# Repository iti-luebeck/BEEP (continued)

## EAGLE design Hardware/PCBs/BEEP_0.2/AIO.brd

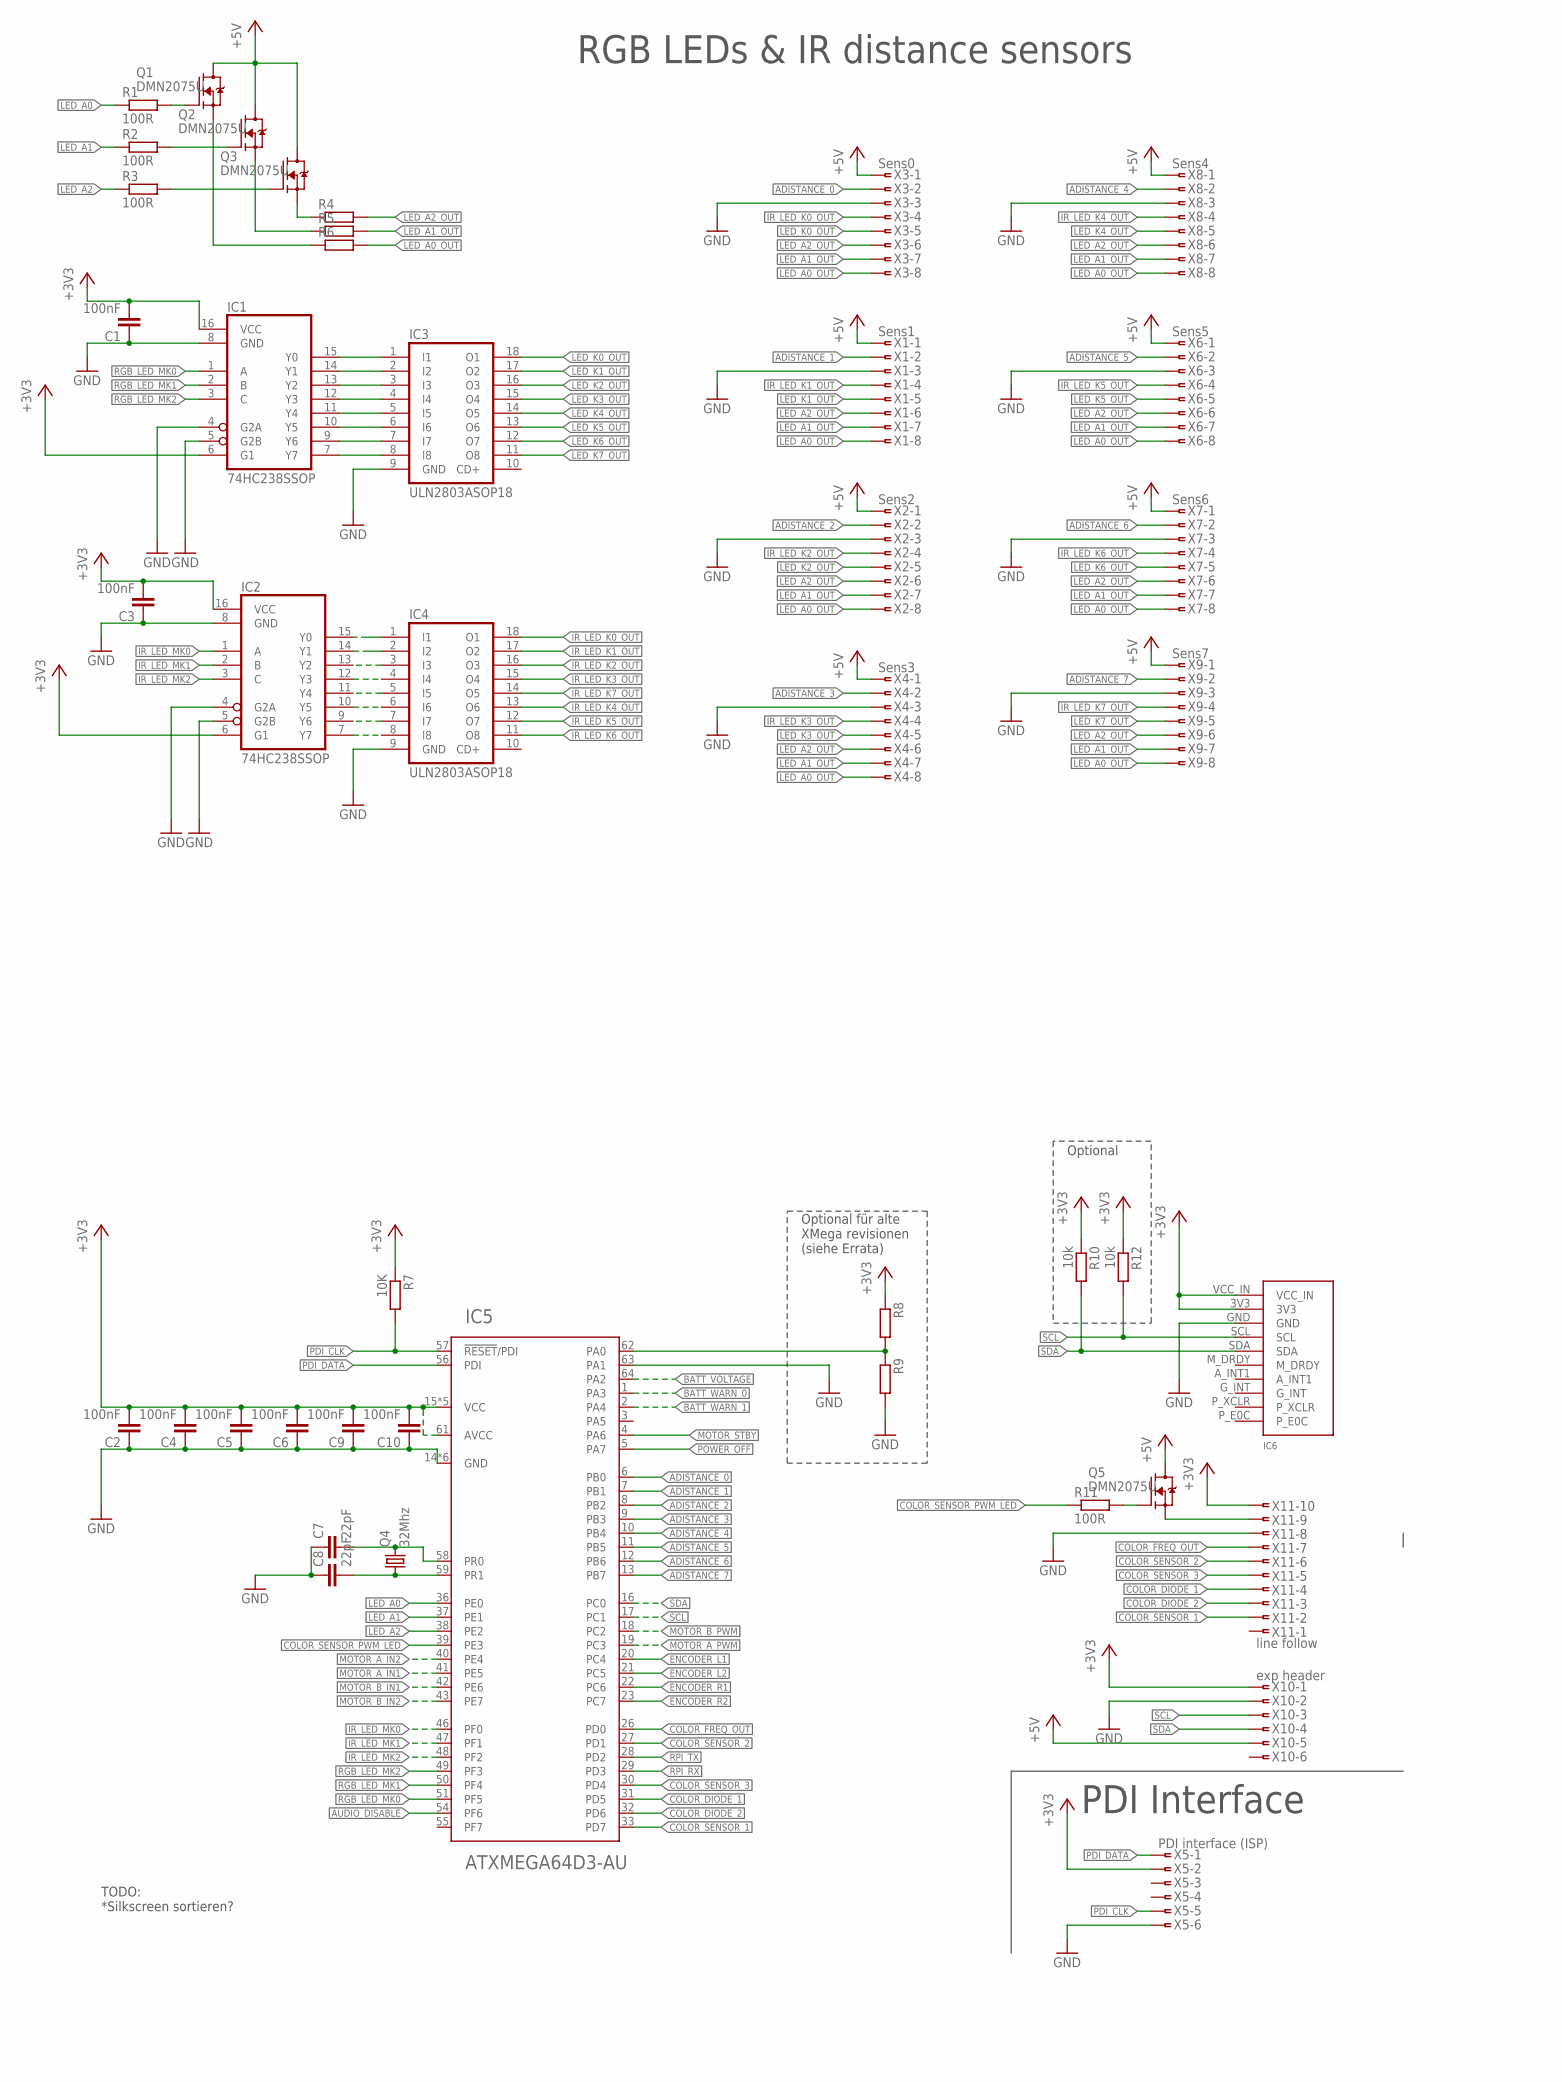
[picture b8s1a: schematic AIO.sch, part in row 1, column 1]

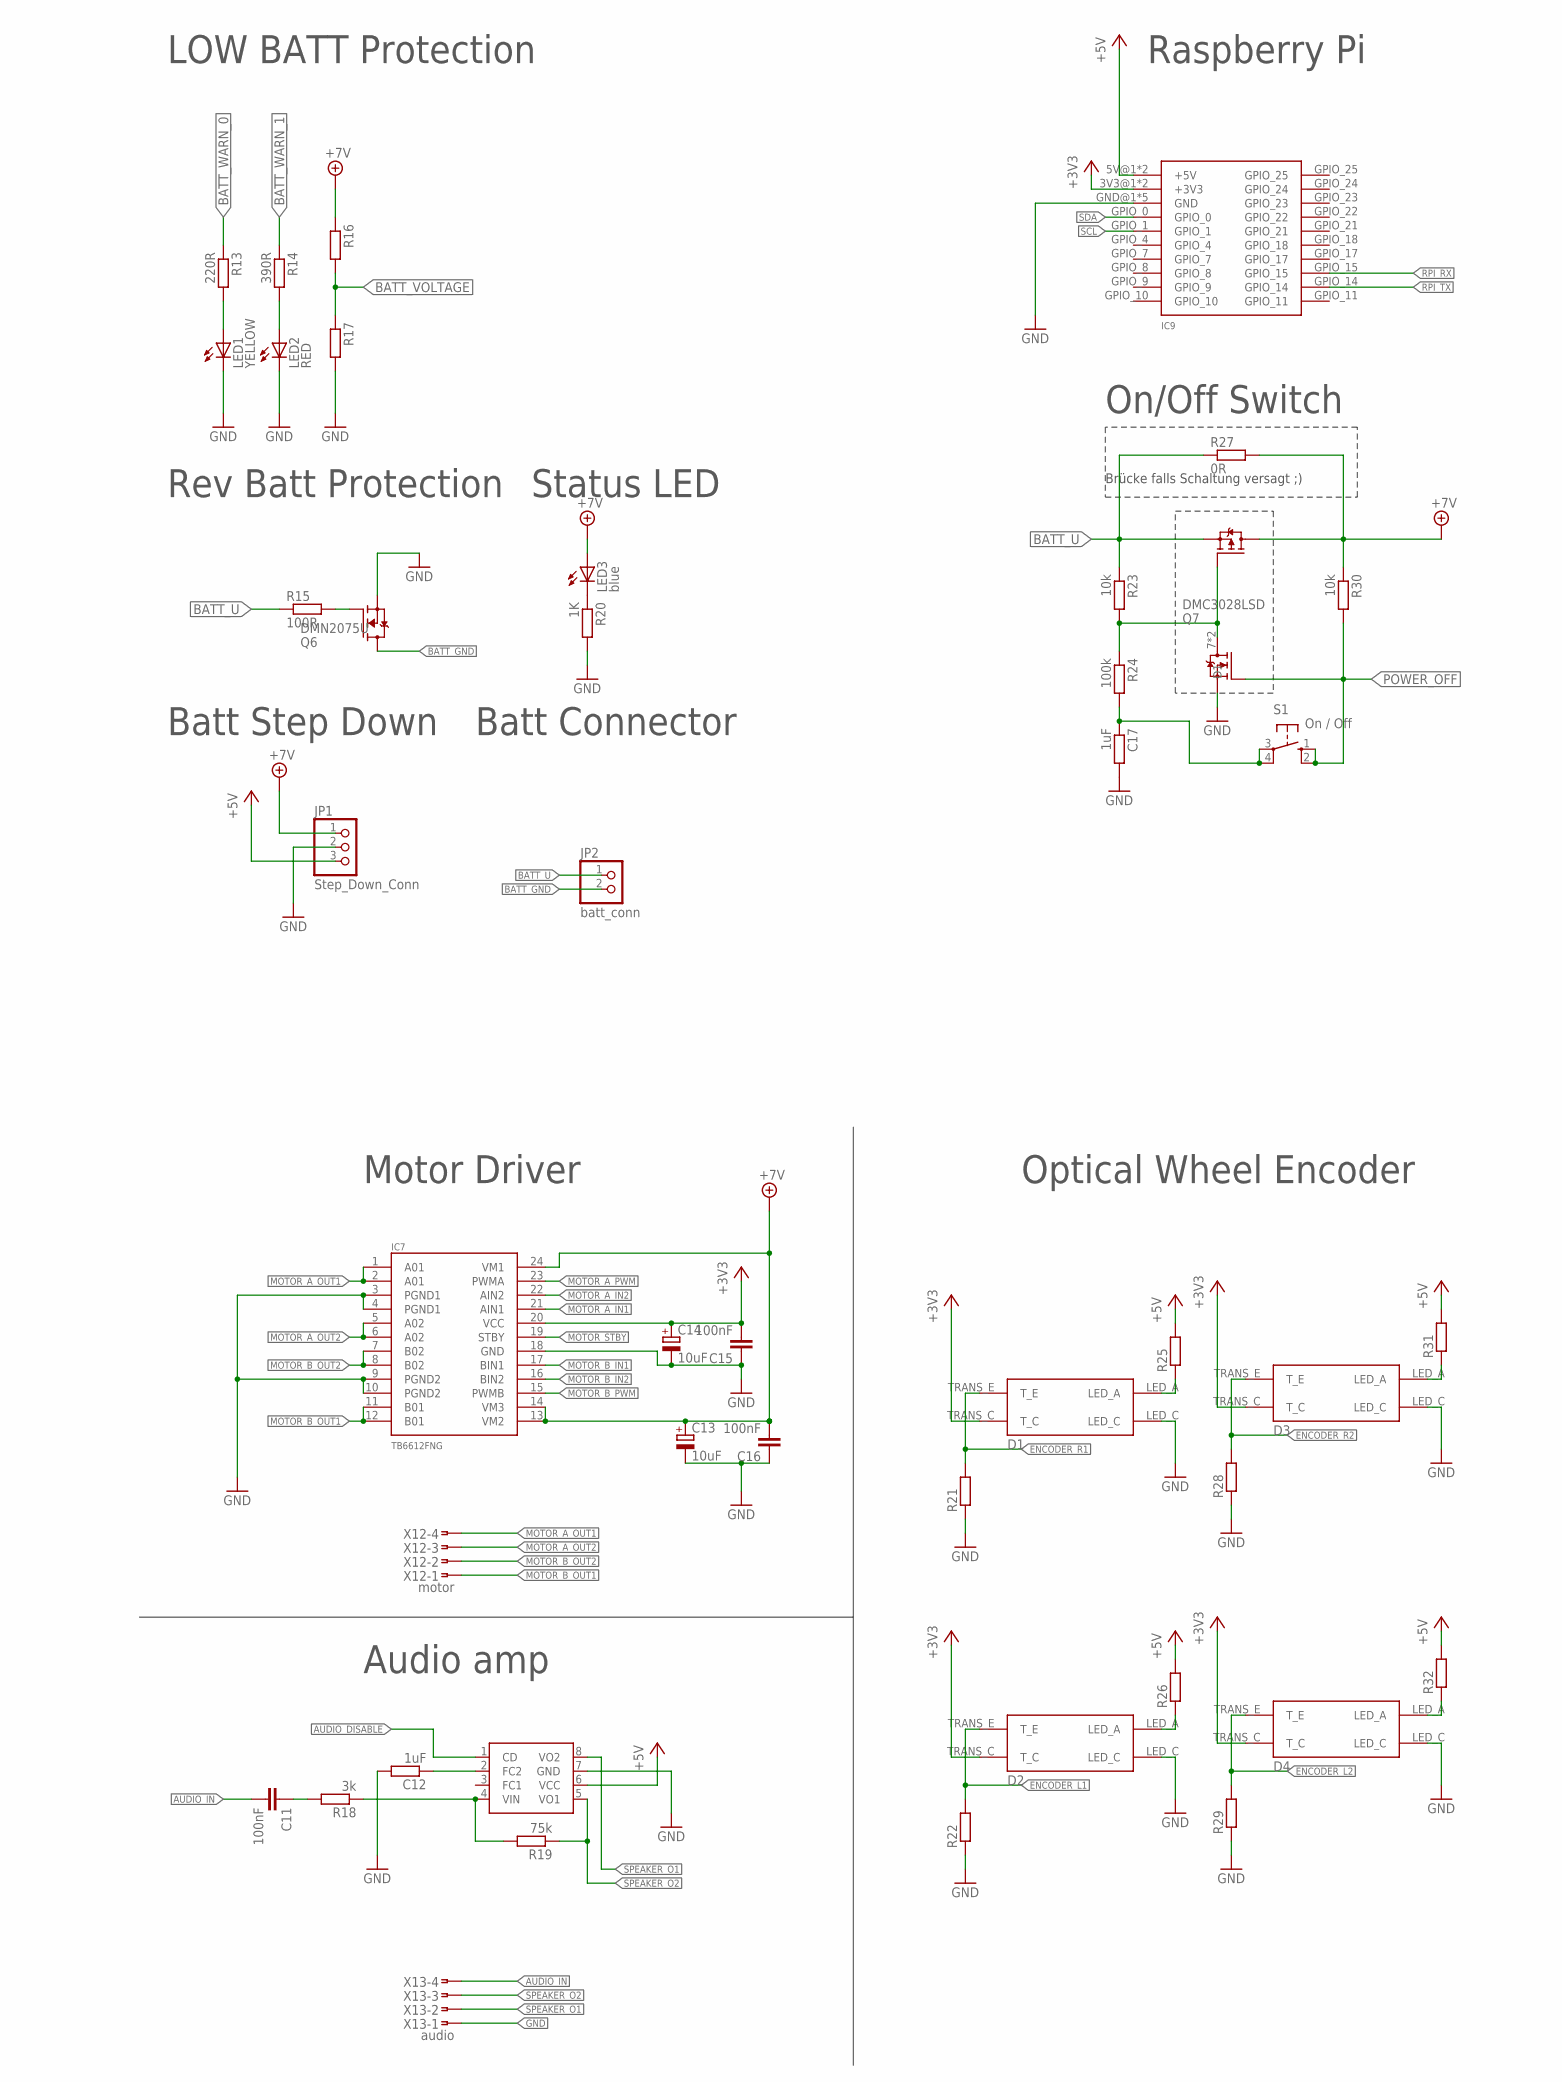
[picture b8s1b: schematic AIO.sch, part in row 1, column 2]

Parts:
C1, C2, C3, C4, C5, C6, C9, C10, C11, C15, C16: 100nF; C0603
C7, C8: 22pF; C0603
C12, C17: 1uF; M0805
C13, C14: 10uF; E2-5
D1, D2, D3, D4: CNY70
IC1, IC2: 74HC238SSOP; SSOP16
IC3, IC4: ULN2803ASOP18; SOP18
IC5: ATXMEGA64D3-AU; TQFP-64A-64
IC6: GY-81
IC7: TB6612FNG; SSOP24
IC8: TS34119SMD; SO08
IC9: RASPBERRY-PI; RASPERRRY-PI
JP1: Step_Down_Conn; 1X03
JP2: batt_conn; 1X02
LED1: YELLOW; CHIPLED_0603
LED2: RED; CHIPLED_0603
LED3: blue; CHIPLED_0603
Q1, Q2, Q3, Q5, Q6: DMN2075U; SOT95P240X112-3N
Q4: 32Mhz; HC18U-V
Q7: DMC3028LSD; SO08
R1, R2, R3, R11, R15: 100R; R0603
R4, R5, R6, R8, R9, R16, R17, R21, R22, R25, R26, R28, R29, R31, R32: R-EU_M0805; M0805
R7: 10K; M0805
R10, R12, R23, R30: 10k; M0805
R13: 220R; M0805
R14: 390R; M0805
R18: 3k; M0805
R19: 75k; M0805
R20: 1K; M0805
R24: 100k; M0805
R27: 0R; M0805
S1: On / Off; B3F-10XX
X1: Sens1; FSIDE-8
X2: Sens2; FSIDE-8
X3: Sens0; FTOP-8
X4: Sens3; FTOP-8
X5: PDI interface (ISP); FTOP-6
X6: Sens5; FSIDE-8
X7: Sens6; FSIDE-8
X8: Sens4; FTOP-8
X9: Sens7; FTOP-8
X10: exp header; FTOP-6
X11: line follow; FTOP-10
X12: motor; FTOP-4
X13: audio; FTOP-4

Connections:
+3V3: C1.2, C2.2, C3.2, C4.2, C5.2, C6.2, C9.2, C10.2, C14.+, C15.2, D1.TRANS_C (T_C), D2.TRANS_C (T_C), D3.TRANS_C (T_C), D4.TRANS_C (T_C), IC1.6 (G1), IC1.16 (VCC), IC2.6 (G1), IC2.16 (VCC), IC5.15 (VCC), IC5.25 (VCC), IC5.35 (VCC), IC5.45 (VCC), IC5.53 (VCC), IC5.61 (AVCC), IC6.3V3, IC6.VCC_IN, IC7.20 (VCC), IC9.3V3@1 (+3V3), IC9.3V3@2 (+3V3), R7.1, R8.1, R10.1, R12.1, X5.2, X10.1, X11.10
+5V: IC8.6 (VCC), IC9.5V@1 (+5V), IC9.5V@2 (+5V), JP1.3, Q1.D, Q2.D, Q3.D, Q5.D, R25.2, R26.2, R31.2, R32.2, X1.1, X2.1, X3.1, X4.1, X6.1, X7.1, X8.1, X9.1, X10.5
+7V: C13.+, C16.2, IC7.13 (VM2), IC7.14 (VM3), IC7.24 (VM1), JP1.1, LED3.A, Q7.5 (D2), Q7.6 (D2), R16.1, R27.2, R30.1
ADISTANCE_0: IC5.6 (PB0), X3.2
ADISTANCE_1: IC5.7 (PB1), X1.2
ADISTANCE_2: IC5.8 (PB2), X2.2
ADISTANCE_3: IC5.9 (PB3), X4.2
ADISTANCE_4: IC5.10 (PB4), X8.2
ADISTANCE_5: IC5.11 (PB5), X6.2
ADISTANCE_6: IC5.12 (PB6), X7.2
ADISTANCE_7: IC5.13 (PB7), X9.2
AUDIO_DISABLE: IC5.54 (PF6), IC8.1 (CD)
AUDIO_IN: C11.2, X13.4
BATT_GND: JP2.2, Q6.D
BATT_U: JP2.1, Q7.3 (S2), R15.1, R23.1, R27.1
BATT_VOLTAGE: IC5.64 (PA2), R16.2, R17.1
BATT_WARN_0: IC5.1 (PA3), R13.1
BATT_WARN_1: IC5.2 (PA4), R14.1
COLOR_DIODE_1: IC5.31 (PD5), X11.4
COLOR_DIODE_2: IC5.32 (PD6), X11.3
COLOR_FREQ_OUT: IC5.26 (PD0), X11.7
COLOR_SENSOR_1: IC5.33 (PD7), X11.2
COLOR_SENSOR_2: IC5.27 (PD1), X11.6
COLOR_SENSOR_3: IC5.30 (PD4), X11.5
COLOR_SENSOR_PWM_LED: IC5.39 (PE3), R11.1
ENCODER_L1: D2.TRANS_E (T_E), IC5.20 (PC4), R22.2
ENCODER_L2: D4.TRANS_E (T_E), IC5.21 (PC5), R29.2
ENCODER_R1: D1.TRANS_E (T_E), IC5.22 (PC6), R21.2
ENCODER_R2: D3.TRANS_E (T_E), IC5.23 (PC7), R28.2
GND: C1.1, C2.1, C3.1, C4.1, C5.1, C6.1, C7.1, C8.1, C9.1, C10.1, C12.2, C13.-, C14.-, C15.1, C16.1, C17.2, D1.LED_C, D2.LED_C, D3.LED_C, D4.LED_C, IC1.4 (G2A), IC1.5 (G2B), IC1.8 (GND), IC2.4 (G2A), IC2.5 (G2B), IC2.8 (GND), IC3.9 (GND), IC4.9 (GND), IC5.14 (GND), IC5.24 (GND), IC5.34 (GND), IC5.44 (GND), IC5.52 (GND), IC5.60 (GND), IC5.63 (PA1), IC6.GND, IC7.3 (PGND1), IC7.4 (PGND1), IC7.9 (PGND2), IC7.10 (PGND2), IC7.18 (GND), IC8.7 (GND), IC9.GND@1 (GND), IC9.GND@2 (GND), IC9.GND@3 (GND), IC9.GND@4 (GND), IC9.GND@5 (GND), JP1.2, LED1.C, LED2.C, Q6.S, Q7.1 (S1), R9.2, R17.2, R20.2, R21.1, R22.1, R28.1, R29.1, X1.3, X2.3, X3.3, X4.3, X5.6, X6.3, X7.3, X8.3, X9.3, X10.2, X11.8, X13.1
IR_LED_K0: IC2.15 (Y0), IC4.1 (I1)
IR_LED_K0_OUT: IC4.18 (O1), X3.4
IR_LED_K1: IC2.14 (Y1), IC4.2 (I2)
IR_LED_K1_OUT: IC4.17 (O2), X1.4
IR_LED_K2_OUT: IC4.16 (O3), X2.4
IR_LED_K3_OUT: IC4.15 (O4), X4.4
IR_LED_K4_OUT: IC4.13 (O6), X8.4
IR_LED_K5_OUT: IC4.12 (O7), X6.4
IR_LED_K6_OUT: IC4.11 (O8), X7.4
IR_LED_K7_OUT: IC4.14 (O5), X9.4
IR_LED_MK0: IC2.1 (A), IC5.46 (PF0)
IR_LED_MK1: IC2.2 (B), IC5.47 (PF1)
IR_LED_MK2: IC2.3 (C), IC5.48 (PF2)
LED_A0: IC5.36 (PE0), R1.1
LED_A0_OUT: R6.2, X1.8, X2.8, X3.8, X4.8, X6.8, X7.8, X8.8, X9.8
LED_A1: IC5.37 (PE1), R2.1
LED_A1_OUT: R5.2, X1.7, X2.7, X3.7, X4.7, X6.7, X7.7, X8.7, X9.7
LED_A2: IC5.38 (PE2), R3.1
LED_A2_OUT: R4.2, X1.6, X2.6, X3.6, X4.6, X6.6, X7.6, X8.6, X9.6
LED_K0_OUT: IC3.18 (O1), X3.5
LED_K1_OUT: IC3.17 (O2), X1.5
LED_K2_OUT: IC3.16 (O3), X2.5
LED_K3_OUT: IC3.15 (O4), X4.5
LED_K4_OUT: IC3.14 (O5), X8.5
LED_K5_OUT: IC3.13 (O6), X6.5
LED_K6_OUT: IC3.12 (O7), X7.5
LED_K7_OUT: IC3.11 (O8), X9.5
MOTOR_A_IN1: IC5.41 (PE5), IC7.21 (AIN1)
MOTOR_A_IN2: IC5.40 (PE4), IC7.22 (AIN2)
MOTOR_A_OUT1: IC7.1 (A01), IC7.2 (A01), X12.4
MOTOR_A_OUT2: IC7.5 (A02), IC7.6 (A02), X12.3
MOTOR_A_PWM: IC5.19 (PC3), IC7.23 (PWMA)
MOTOR_B_IN1: IC5.42 (PE6), IC7.17 (BIN1)
MOTOR_B_IN2: IC5.43 (PE7), IC7.16 (BIN2)
MOTOR_B_OUT1: IC7.11 (B01), IC7.12 (B01), X12.1
MOTOR_B_OUT2: IC7.7 (B02), IC7.8 (B02), X12.2
MOTOR_B_PWM: IC5.18 (PC2), IC7.15 (PWMB)
MOTOR_STBY: IC5.4 (PA6), IC7.19 (STBY)
unnamed: Q3.S, R4.1
unnamed: Q2.S, R5.1
unnamed: Q1.S, R6.1
unnamed: IC5.62 (PA0), R8.2, R9.1
unnamed: Q5.S, X11.9
unnamed: IC2.13 (Y2), IC4.3 (I3)
unnamed: IC2.12 (Y3), IC4.4 (I4)
unnamed: Q6.G, R15.2
unnamed: IC2.11 (Y4), IC4.5 (I5)
unnamed: IC2.10 (Y5), IC4.6 (I6)
unnamed: D4.LED_A, R32.1
unnamed: IC2.9 (Y6), IC4.7 (I7)
unnamed: IC2.7 (Y7), IC4.8 (I8)
unnamed: C8.2, IC5.59 (PR1), Q4.1
unnamed: IC8.4 (VIN), R18.1, R19.2
unnamed: C17.1, R24.2, S1.3, S1.4 (P1)
unnamed: C11.1, R18.2
unnamed: C7.2, IC5.58 (PR0), Q4.2
unnamed: LED3.C, R20.1
unnamed: D1.LED_A, R25.1
unnamed: IC1.15 (Y0), IC3.1 (I1)
unnamed: Q7.4 (G2), Q7.7 (D1), Q7.8 (D1), R23.2, R24.1
unnamed: D2.LED_A, R26.1
unnamed: IC1.14 (Y1), IC3.2 (I2)
unnamed: Q5.G, R11.2
unnamed: D3.LED_A, R31.1
unnamed: IC1.13 (Y2), IC3.3 (I3)
unnamed: IC1.12 (Y3), IC3.4 (I4)
unnamed: LED2.A, R14.2
unnamed: IC1.11 (Y4), IC3.5 (I5)
unnamed: IC1.10 (Y5), IC3.6 (I6)
unnamed: LED1.A, R13.2
unnamed: IC1.9 (Y6), IC3.7 (I7)
unnamed: IC1.7 (Y7), IC3.8 (I8)
unnamed: C12.1, IC8.2 (FC2)
unnamed: Q1.G, R1.2
unnamed: Q2.G, R2.2
unnamed: Q3.G, R3.2
PDI_CLK: IC5.57 (!RESET!/PDI), R7.2, X5.5
PDI_DATA: IC5.56 (PDI), X5.1
POWER_OFF: IC5.5 (PA7), Q7.2 (G1), R30.2, S1.1 (S), S1.2 (S1)
RGB_LED_MK0: IC1.1 (A), IC5.51 (PF5)
RGB_LED_MK1: IC1.2 (B), IC5.50 (PF4)
RGB_LED_MK2: IC1.3 (C), IC5.49 (PF3)
RPI_RX: IC5.29 (PD3), IC9.GPIO_15
RPI_TX: IC5.28 (PD2), IC9.GPIO_14
SCL: IC5.17 (PC1), IC6.SCL, IC9.GPIO_1, R12.2, X10.3
SDA: IC5.16 (PC0), IC6.SDA, IC9.GPIO_0, R10.2, X10.4
SPEAKER_O1: IC8.8 (VO2), X13.2
SPEAKER_O2: IC8.5 (VO1), R19.1, X13.3

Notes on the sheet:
Motor Driver
Optical Wheel Encoder
RGB LEDs & IR distance sensors
PDI Interface
Rev Batt Protection
LOW BATT Protection
Raspberry Pi
Batt Step Down
Batt Connector
On/Off Switch
Status LED
Audio amp
Optional
Optional für alte XMega revisionen (siehe Errata)
Brücke falls Schaltung versagt ;)
TODO: *Silkscreen sortieren?

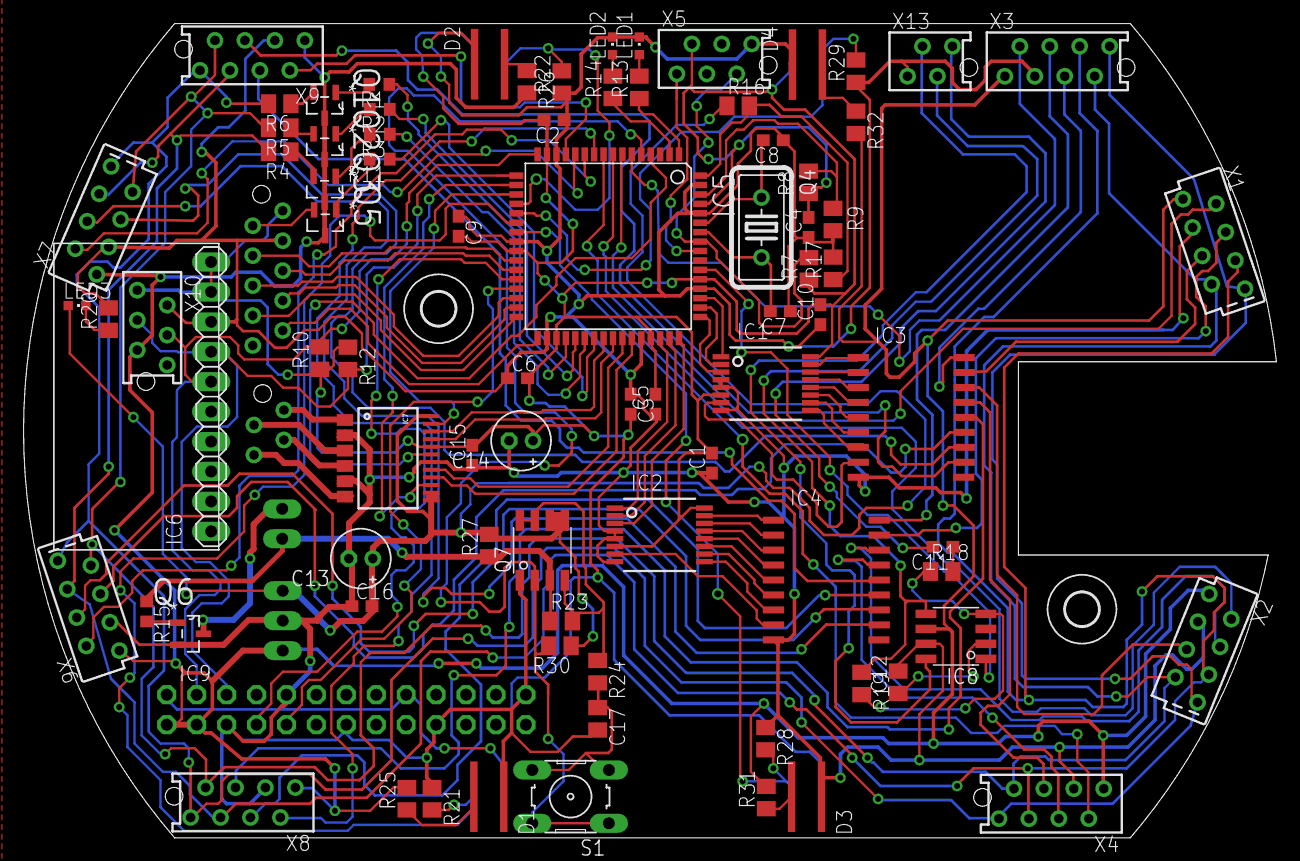
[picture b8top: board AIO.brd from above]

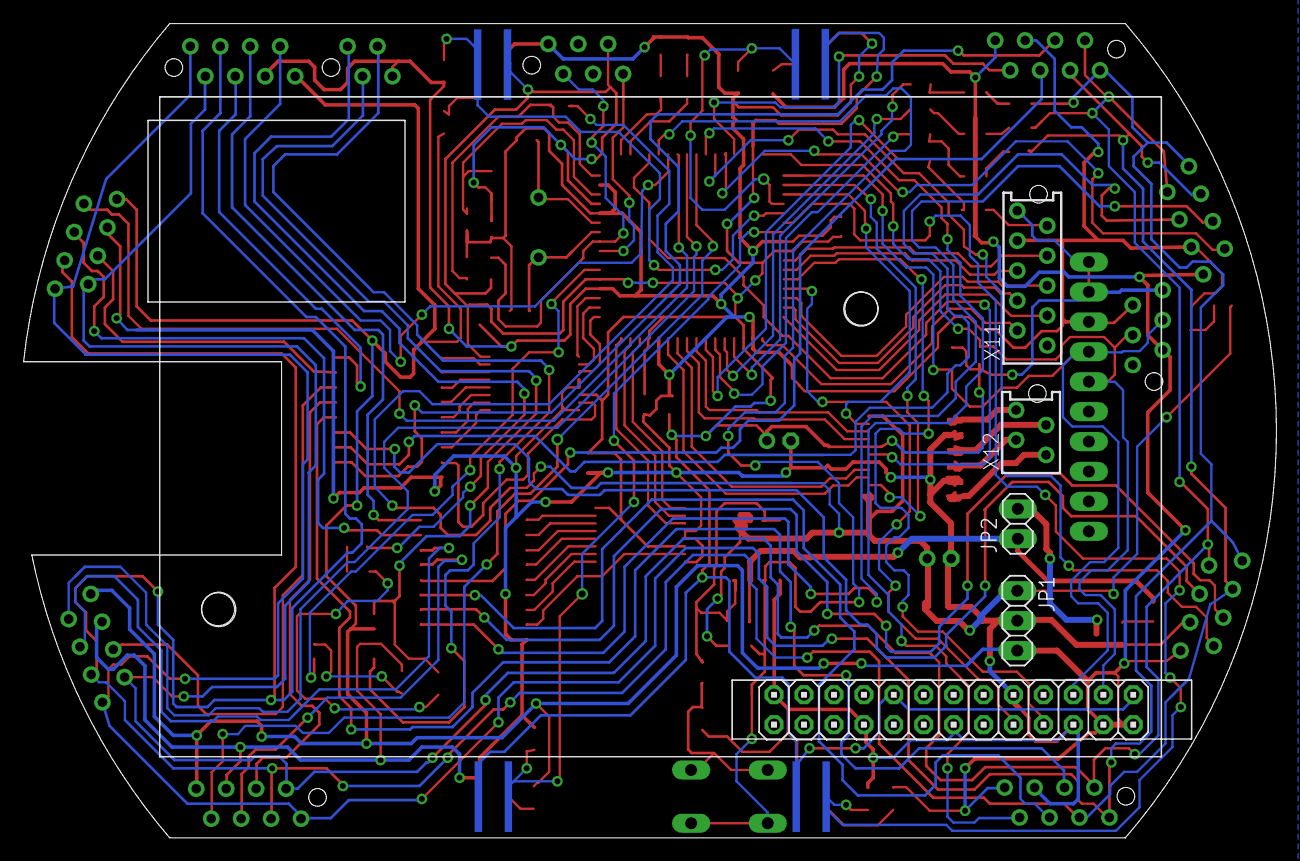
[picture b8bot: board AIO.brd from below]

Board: 2 copper layers, 106.3 x 69.1 mm, 91 parts (5 on the bottom side), 118 nets.

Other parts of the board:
U$1: COPPER7
U$4, U$6: 2,8

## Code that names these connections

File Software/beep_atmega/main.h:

#ifndef AVR205_FREQUENCY_MEASURE_INTERRUPT_H_
#define AVR205_FREQUENCY_MEASURE_INTERRUPT_H_

#include <avr/io.h>
#include <compat/ina90.h>
#include <avr/interrupt.h>
#include "freq_meter.h"
#include <util/delay.h>
#include <avr/pgmspace.h>


/*! \brief  Measures color and stores value in last_color_freq
 *
 *  \note  this methode uses the scaleFactors to scale to a correct part of the rgb value. Call calibrateColor first.
 */
void measure_color(uint8_t color);

/*! \brief  stores the scaleFactors while measuring white.
 *
 *  \note  let the sensore see white, when calibrating.
 */
void calibrateColor();

void setup_rgb_leds();



volatile uint8_t last_color_freq[4];	//last measured values
volatile float scaleFactors[4];			//values to scale to rgb values
volatile uint8_t calibrate;				//flag to indicate the main to calibrate the scaleFactors

//ground colorsensor
#define S2				PB0 //uses PD6 and PD7 to set color for measurement
#define S3				PB1
#define COLOR_BIT_MASK	0xff & ~((1<<S2)|(1<<S3))

//LEDs
#define PWM_R 

#endif /* AVR205_FREQUENCY_MEASURE_INTERRUPT_H_ */

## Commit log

2013-02-09 Added node publishing an (not finished) imu msg
2013-04-19 Test commit.
2013-04-29 initialize .gitignore commit prototype boards
2013-04-29 enlarge Clearence to 10mil created some pdf files for the boards
2013-05-05 Add branding ;) enhance PCBs finish Easy RGB Board add Texas Instruments libray from Element 14 add dxf import ulp for eagle add Script for easy eagle export to pdf for etching minor cleanup
2013-05-05 remove eagle history files from git
2013-05-05 cleanup
2013-05-06 add all in one pdf for etching
2013-05-10 remove GND under TSL2671 fix LED size fix Cap size
2013-05-15 update HSDL-9100 footprint and pcb
2013-05-16 rotate reset button on atmega board remove GND under TCS3103
2013-05-17 add BEEP atmega code
2013-05-17 add color test page
2013-05-23 add initial 3D plans
2013-05-24 add lot of 3D sketches. Needs some cleanup.
2013-05-28 add transmission really needs some cleanup!
2013-05-28 Remove Inventor Backups
2013-05-31 add two experimental gear systems
2013-06-03 minor harware moel changes
2013-06-03 enhance GetriebeB add cnc version of GetriebeB
2013-06-04 Enhance Getriebe B cnc lodistance
2013-06-04 create g code for gear system
2013-06-06 add some drill files etc.
2013-06-06 add EE-SX1131 electronic
2013-06-13 enhance HSDL-9100 electronic
2013-06-14 enhance pads and board for HSDL-9100
2013-06-14 edit version String
2013-06-24 add some eagle libraries add BEEP AIO Board
2013-06-25 Big Cleanup: * new folder structure under Hardware * new CAD models for wheels, gear motor, batteries, battery holder, etc
2013-06-25 Fix battery names, enhance model
2013-06-26 minor tweaks to 3D CAD models
2013-06-26 Begin with the case and the asus xtionPRO LIVE
2013-06-27 enhance case add HSDL-9100 add holes for HSDL-9100
2013-06-28 enhance robot case enhance main circuit
2013-06-28 minor enhancement of robot case enhancements of RPi Footprint enhance main pcb add pcb space drawing
2013-06-28 add dxf, ps files for pcb dimensions
2013-06-28 change dxf to mm format remove ps file enhance tips file for eagle dxf inmport
2013-06-28 try again to export with mm
2013-06-28 use LINE instead of POLYLINE in DXF
2013-06-28 try another dxf export
2013-06-28 add robot pcb space to eagle pcb enhance circuit
2013-07-01 enhance BEEP main pcb, rgb and ir boards
2013-07-01 continue working on shematic for AIO BEEP started with pcb routing
2013-07-03 partly route the main beep board
2013-07-03 continue routing
2013-07-25 *add i2c connector *continue routing
2013-07-25 add i2c header continue routing
2013-07-25 added some testnodes to catkin workspace catkin will not be used und probably deleted with the next commit added ir_distance and zusmoro_state_machine rosbuild package
2013-07-26 Added ros stack beep_framework containing all nodes and messages
2013-07-26 continue routing add hardware architecture shematic
2013-07-29 add momentary push button with mosfet latch circuit as on/off switch continue routing
2013-07-29 continue routing replace so16 multiplexer with ssop16 add ssop16 footprint to beep library
2013-07-30 continue routing...
2013-07-31 restructured sensor architecture
2013-07-31 Add audio amplifier correct batt rev circuit and on off circuit some routing
2013-07-31 routing
2013-07-31 add critical DRC file continue routing
2013-07-31 change folder structure and naming shema
2013-07-31 further cleanup
2013-07-31 add poweroff line to atxmega
2013-08-01 enhance routing fix rgb and ir distance board (connector was on the wrong side)
2013-08-01 rearrange connectors routing
2013-08-02 move folders try to apply drc from sparkfun (wip) moved audio connetor add slice for camera flexcable
2013-08-02 beep node requests all sensor data from xmega and publishes them on topics beep node also can be used to send actuator commands to xmega by publishing on topics
2013-08-22 enhance routing, add external crystal, move components for Raspberry Pi
2013-08-23 Use PORTC for TWI, bcause of really annoying errata that states that TWI on PORT E is unusable for Revisions prior of I. damn errata!!!
2013-08-24 minor enhancements
2013-08-24 add 3M 8526-4500PL to RPi drawing and adjust PCB change keepout to restrict layer for usb and network port locations
2013-08-24 add lib for modified micromatch connector (with orietation hole) use micromatch connector with orientation hole
2013-08-24 add some 3D rendering of the PCB
2013-08-25 minor pcb changes add 3D model of main pcb to 3d CAD folder clean up
2013-08-26 continue work on 3D model and replace connector for ir rgb board
2013-08-26 update hardware architecture graphic
2013-08-26 recover sch from trash... :-/
2013-08-26 change most 0603 components to 0805 change smd Typ D Footprint to THT Footprint
2013-08-27 enhance 3D model
2013-08-27 minor enhancement of symbol placement
2013-08-27 add connections from xmega to encoders enhance Borders
2013-08-27 minor pcb changes
2013-08-27 last? minor changes.
2013-08-30 modelling 3D model of case, minor change of ir / rgb board
2013-08-30 change value of cap in of off circuit continue case design
2013-09-05 add new parts
2013-09-09 enhance case
2013-09-09 add 3D CAD render and images of the pcb
2013-09-10 add simulation
2013-09-10 add irlml2244 to pwm simulation
2013-09-10 add IRLML2244 transistor to library add pcb to fix heigh side driver
2013-09-13 add in development XMega Code
2013-09-13 Case modifications: *add stand for ball caster *add mounting hole >>This is the 3D printed case<<
2013-09-16 some xMega changes
2013-09-16 add images of BEEP 0.2 case
2013-09-16 rename files add bottom board (WIP)
2013-09-17 add encoder wheel inlay add ods file to calculate XMega baud rate
2013-09-18 add simulation for comperator with hysteresis add library with atmel products (by element14) continue work on bottom shematic
2013-09-18 add side sensor board
2013-09-19 add more distance boards continue work on bottom pcb
2013-09-20 started routing of the bottom pcb
2013-09-20 continue work on bottom pcb
2013-09-23 continue work on bottom pcbs
2013-09-26 fix conflicting Color message by renaming to MyColor (someone might want to use some more usefull prefix)
2013-09-26 continue work on bottom pcb add simulation for attiny on/off
2013-09-26 add modified gcode export script finish bottom pcb add gcode for cnc
2013-10-09 Updated Baudrate in beep.py
2013-10-09 change baud rate to match the atxmega
2013-10-11 add 74hcxx spice models add new enhanced attiny on off circuit (rev2=pmos, rev3=nmos and experimental)
2013-10-11 fix simulation of on/off switch add attiny on off switch code add latest xmega code changes
2013-10-15 correct encoder on bottom pcb enhance attiny code
2013-12-19 the forgotten commit ;)
    * enhance bottom, rgb sensor pcb
    * create attiny and lm239 eval boards
    * bug fix for the pdf export scripts
    * correct attiny soft power switch simulation
    * add experimental color sensor code
    * add rgb color look up table
2014-01-06 Add new color calibration values
2014-01-09 updated 3d CAD models. Add exploded view. Add blender rendering + image.
2014-01-09 added measurement-evaluation of IR-filter
2014-01-10 use mean instead of sum to calculate the mean sdt derivation of the color calibration
2015-10-06 - added license file and readme
